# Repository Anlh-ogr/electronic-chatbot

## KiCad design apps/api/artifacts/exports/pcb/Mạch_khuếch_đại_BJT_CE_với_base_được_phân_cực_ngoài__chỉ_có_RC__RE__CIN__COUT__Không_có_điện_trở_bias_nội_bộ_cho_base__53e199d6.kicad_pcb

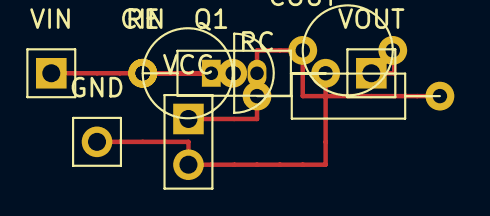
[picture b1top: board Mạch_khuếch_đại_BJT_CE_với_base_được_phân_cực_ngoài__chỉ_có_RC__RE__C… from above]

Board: 2 copper layers, 9 parts (0 on the bottom side), 7 nets.

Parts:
CIN: CAPACITOR; CP_Radial_D5.0mm_P2.50mm
COUT: CAPACITOR; CP_Radial_D5.0mm_P2.50mm
GND: GROUND; PinHeader_1x01_P2.54mm_Vertical
Q1: BJT; TO-92_Inline
RC: RESISTOR; R_Axial_DIN0207_L6.3mm_D2.5mm_P10.16mm_Vertical
RE: RESISTOR; R_Axial_DIN0207_L6.3mm_D2.5mm_P10.16mm_Vertical
VCC: VOLTAGE_SOURCE; PinHeader_1x02_P2.54mm_Vertical
VIN: PORT; PinHeader_1x01_P2.54mm_Vertical
VOUT: PORT; PinHeader_1x01_P2.54mm_Vertical

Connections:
net_base: CIN.1, Q1.2
net_collector: COUT.1, Q1.3, RC.2
net_emitter: Q1.1, RE.1
net_gnd: GND.1, RE.2, VCC.2
net_in: CIN.2, VIN.1
net_out: COUT.2, VOUT.1
net_vcc: RC.1, VCC.1
